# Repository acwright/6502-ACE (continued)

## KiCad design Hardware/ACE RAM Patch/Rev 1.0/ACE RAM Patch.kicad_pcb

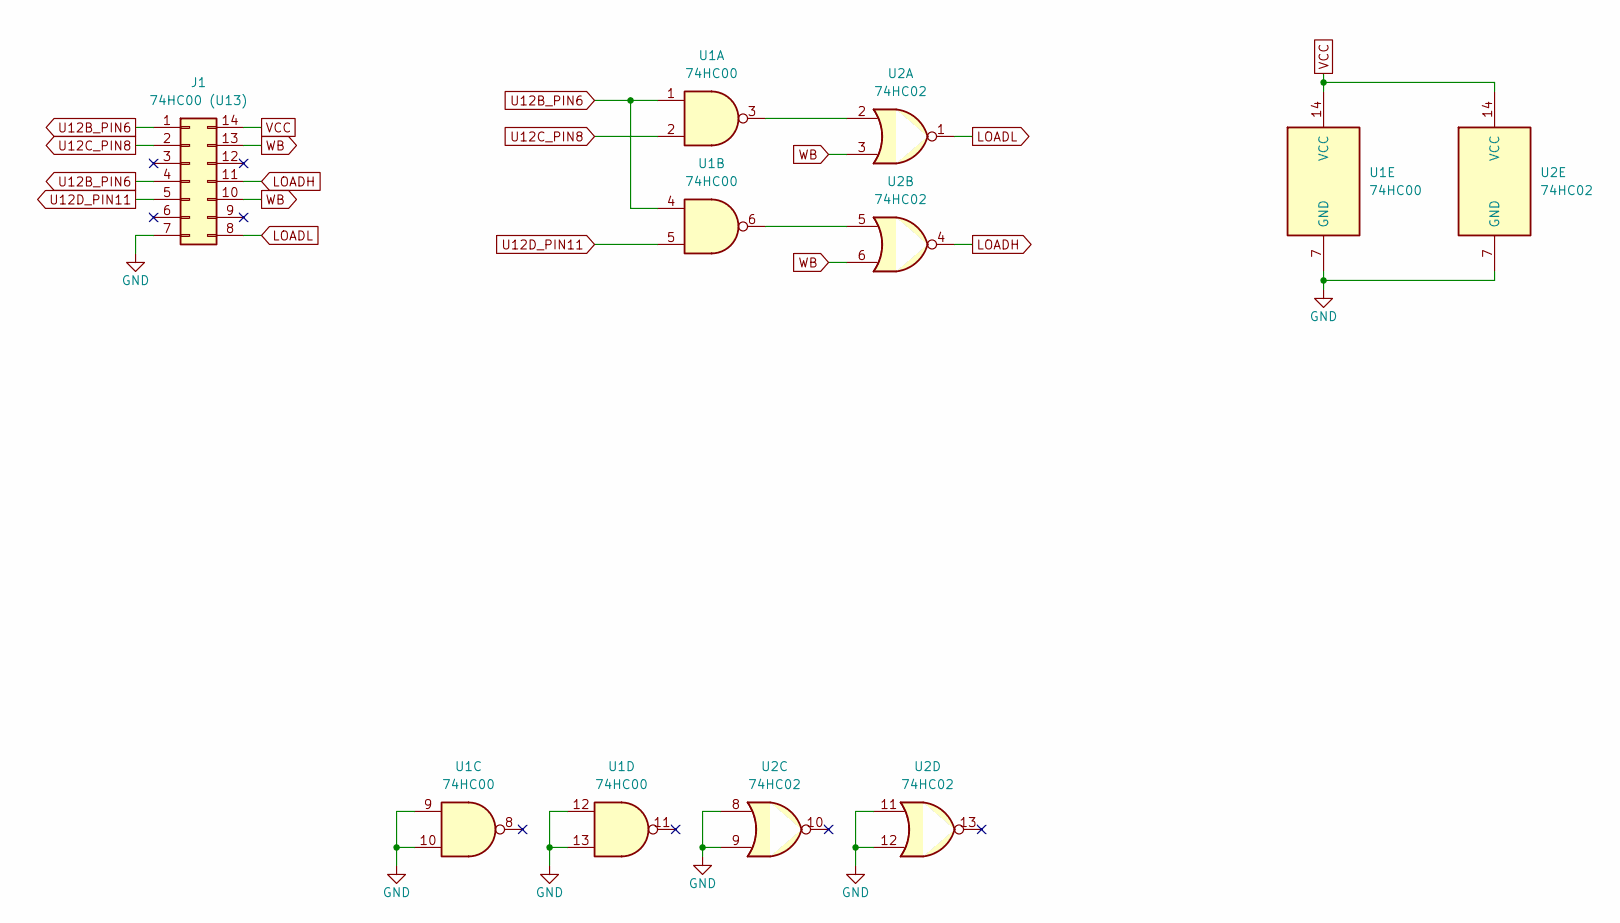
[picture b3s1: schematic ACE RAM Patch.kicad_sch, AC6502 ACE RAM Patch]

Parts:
J1: 74HC00 (U13); DIP-14_W7.62mm_LongPads; Digikey 296-1563-5-ND
U1: 74HC00; DIP-14_W7.62mm_LongPads; Digikey 296-1563-5-ND
U2: 74HC02; DIP-14_W7.62mm_LongPads; Digikey 296-1564-5-ND

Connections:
GND: J1.7, U1.7 (GND), U1.9, U1.10, U1.12, U1.13, U2.7 (GND), U2.8, U2.9, U2.11, U2.12
LOADH: J1.11, U2.4
LOADL: J1.8, U2.1
unnamed: U1.3, U2.2
unnamed: U1.6, U2.5
U12B_PIN6: J1.1, J1.4, U1.1, U1.4
U12C_PIN8: J1.2, U1.2
U12D_PIN11: J1.5, U1.5
VCC: J1.14, U1.14 (VCC), U2.14 (VCC)
WB: J1.10, J1.13, U2.3, U2.6

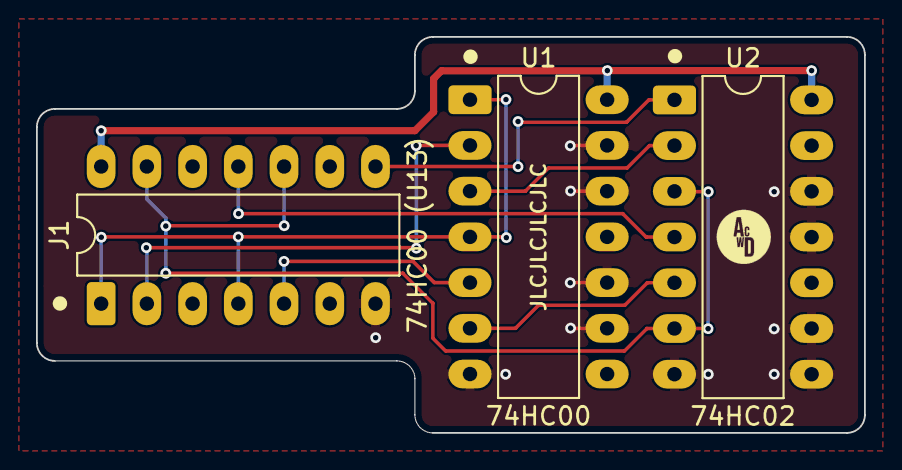
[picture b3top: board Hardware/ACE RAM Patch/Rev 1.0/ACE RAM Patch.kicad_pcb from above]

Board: 2 copper layers, 46.0 x 22.0 mm, 3 parts (0 on the bottom side), 10 nets.

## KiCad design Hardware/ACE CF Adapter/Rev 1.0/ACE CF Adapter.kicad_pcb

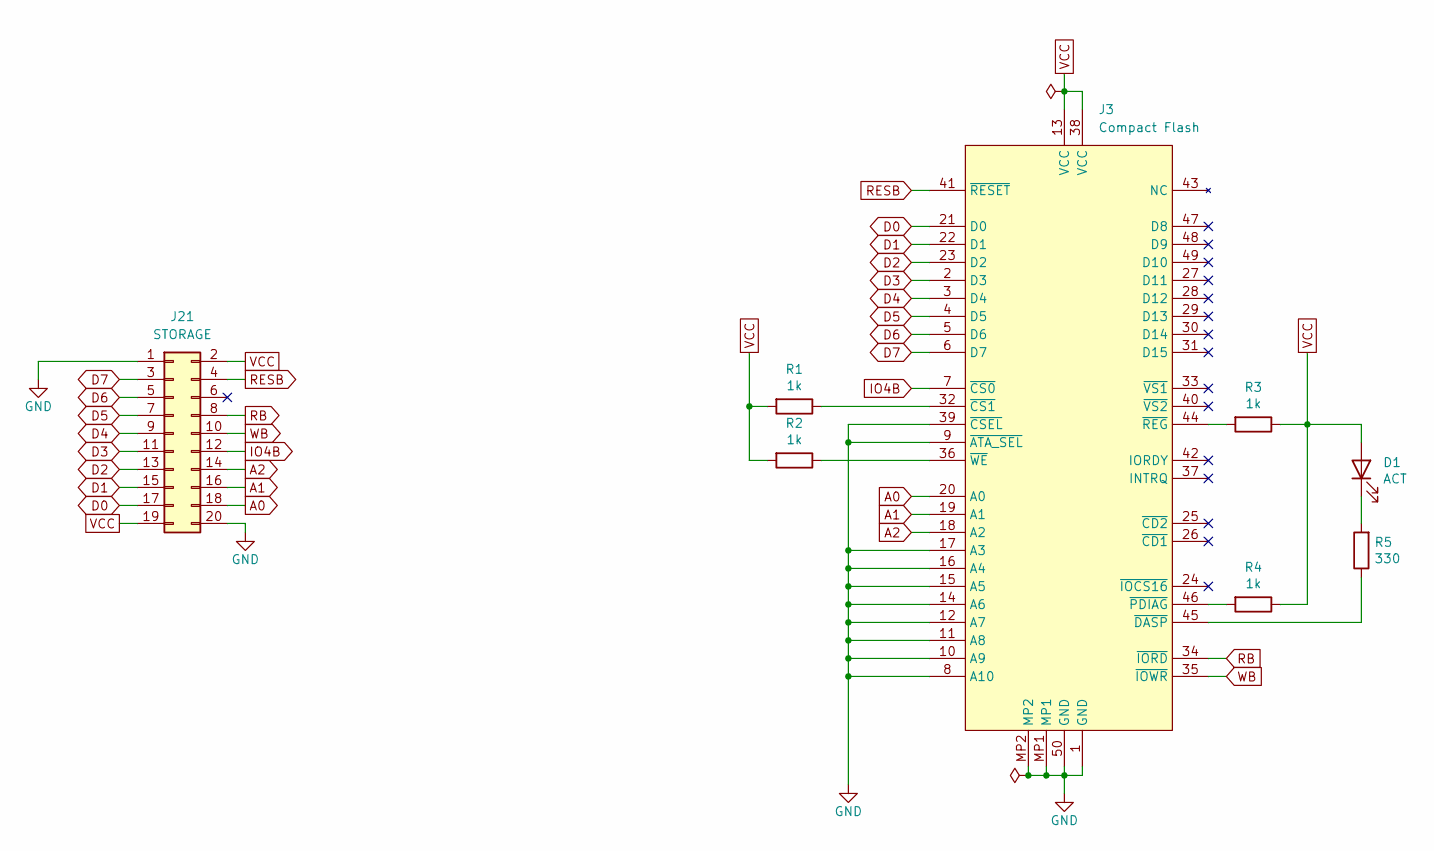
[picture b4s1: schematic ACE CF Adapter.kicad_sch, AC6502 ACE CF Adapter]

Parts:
D1: ACT; LED_D3.0mm; Digikey 732-5008-ND
J3: Compact Flash; CompactFlash Socket; Digikey 4827-101D-TAAB-R01-ND
J21: STORAGE; PinHeader_2x10_P2.54mm_Horizontal; Digikey 609-3338-ND
R1, R2, R3, R4: 1k; R_Axial_DIN0204_L3.6mm_D1.6mm_P5.08mm_Horizontal; Digikey 13-MFR-12FTF52-1KCT-ND
R5: 330; R_Axial_DIN0204_L3.6mm_D1.6mm_P5.08mm_Horizontal; Mouser 603-MFR-12FTF52-330R

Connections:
A0: J3.20 (A0), J21.18
A1: J3.19 (A1), J21.16
A2: J3.18 (A2), J21.14
D0: J3.21 (D0), J21.17
D1: J3.22 (D1), J21.15
D2: J3.23 (D2), J21.13
D3: J3.2 (D3), J21.11
D4: J3.3 (D4), J21.9
D5: J3.4 (D5), J21.7
D6: J3.5 (D6), J21.5
D7: J3.6 (D7), J21.3
GND: J3.1 (GND), J3.8 (A10), J3.9 (~ATA_SEL), J3.10 (A9), J3.11 (A8), J3.12 (A7), J3.14 (A6), J3.15 (A5), J3.16 (A4), J3.17 (A3), J3.39 (~CSEL), J3.50 (GND), J3.MP1, J3.MP2, J21.1, J21.20
IO4B: J3.7 (~CS0), J21.12
unnamed: D1.1 (K), R5.2
unnamed: J3.32 (~CS1), R1.1
unnamed: J3.45 (~DASP), R5.1
unnamed: J3.46 (~PDIAG), R4.2
unnamed: J3.44 (~REG), R3.2
unnamed: J3.36 (~WE), R2.1
RB: J3.34 (~IORD), J21.8
RESB: J3.41 (~RESET), J21.4
VCC: D1.2 (A), J3.13 (VCC), J3.38 (VCC), J21.2, J21.19, R1.2, R2.2, R3.1, R4.1
WB: J3.35 (~IOWR), J21.10

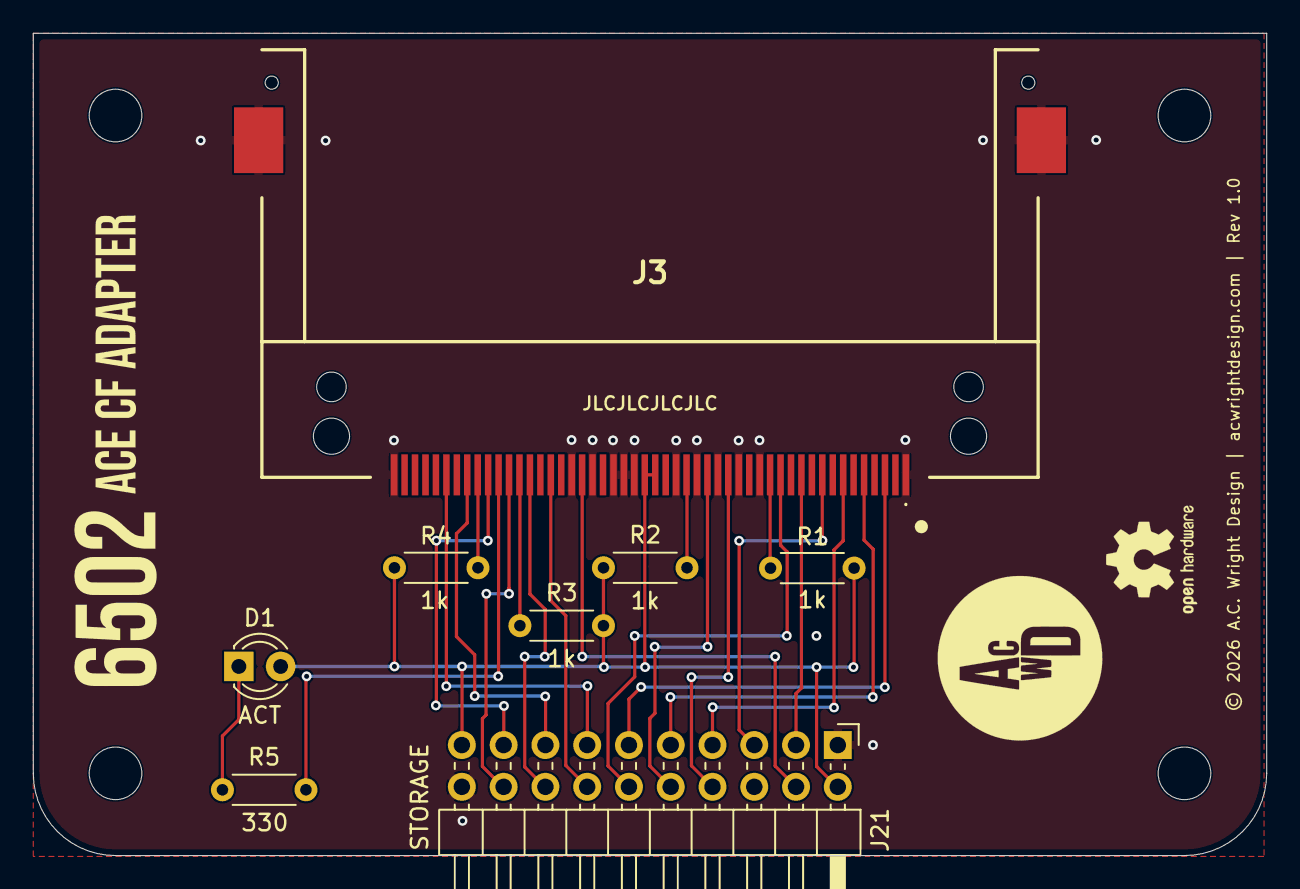
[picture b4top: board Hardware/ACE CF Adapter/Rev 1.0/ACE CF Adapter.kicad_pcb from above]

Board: 2 copper layers, 75.0 x 50.0 mm, 8 parts (0 on the bottom side), 23 nets.

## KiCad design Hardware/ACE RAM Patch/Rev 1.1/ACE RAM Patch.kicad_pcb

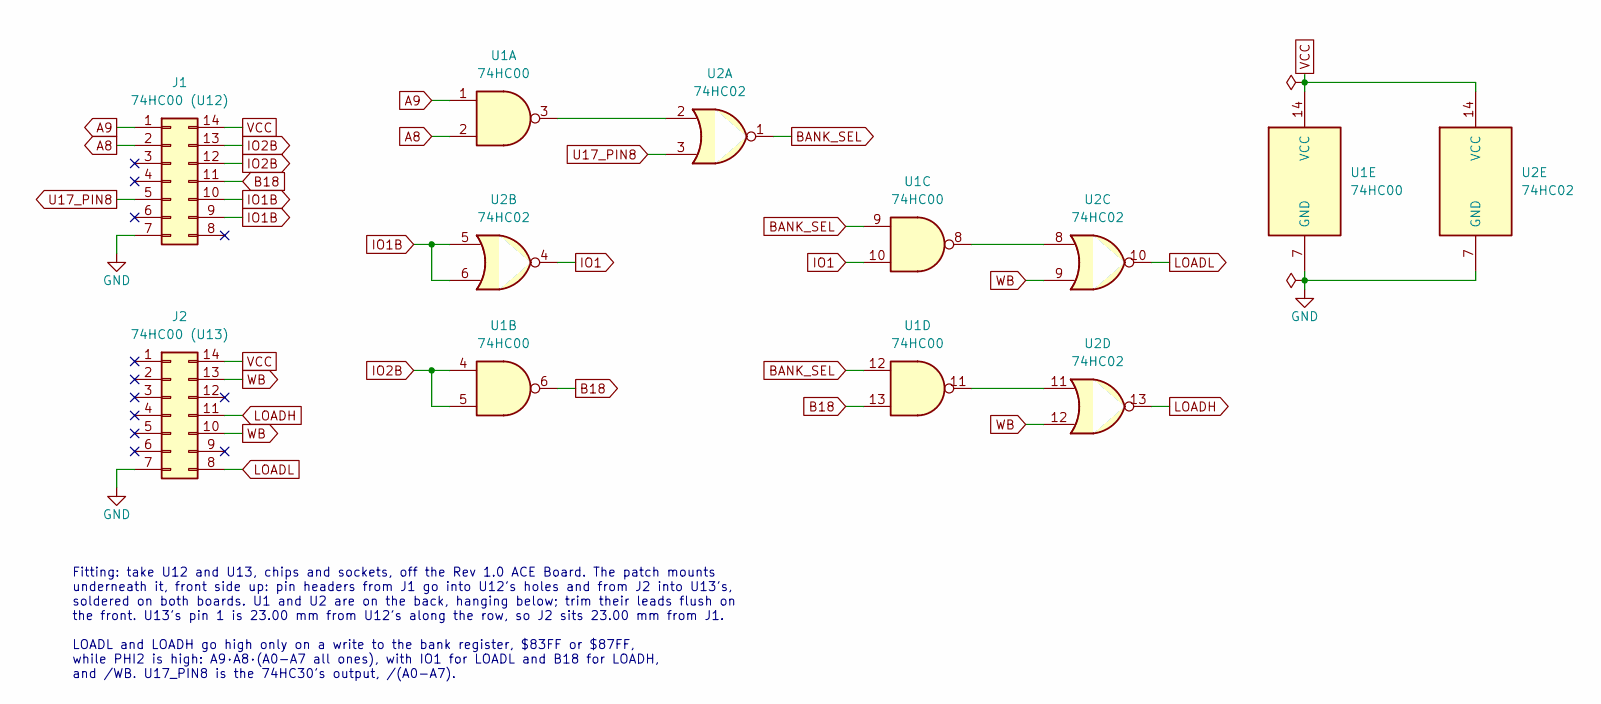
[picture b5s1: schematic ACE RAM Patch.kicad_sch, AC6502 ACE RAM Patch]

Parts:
J1: 74HC00 (U12); DIP-14_W7.62mm_LongPads; Digikey 296-1563-5-ND
J2: 74HC00 (U13); DIP-14_W7.62mm_LongPads; Digikey 296-1563-5-ND
U1: 74HC00; DIP-14_W7.62mm_LongPads; Digikey 296-1563-5-ND
U2: 74HC02; DIP-14_W7.62mm_LongPads; Digikey 296-1564-5-ND

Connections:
A8: J1.2, U1.2
A9: J1.1, U1.1
B18: J1.11, U1.6, U1.13
BANK_SEL: U1.9, U1.12, U2.1
GND: J1.7, J2.7, U1.7 (GND), U2.7 (GND)
IO1: U1.10, U2.4
IO1B: J1.9, J1.10, U2.5, U2.6
IO2B: J1.12, J1.13, U1.4, U1.5
LOADH: J2.11, U2.13
LOADL: J2.8, U2.10
unnamed: U1.3, U2.2
unnamed: U1.8, U2.8
unnamed: U1.11, U2.11
U17_PIN8: J1.5, U2.3
VCC: J1.14, J2.14, U1.14 (VCC), U2.14 (VCC)
WB: J2.10, J2.13, U2.9, U2.12

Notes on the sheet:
Fitting: take U12 and U13, chips and sockets, off the Rev 1.0 ACE Board. The patch mounts underneath it, front side up: pin headers from J1 go into U12's holes and from J2 into U13's, soldered on both boards. U1 and U2 are on the back, hanging below; trim their leads flush on the front. U13's pin 1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

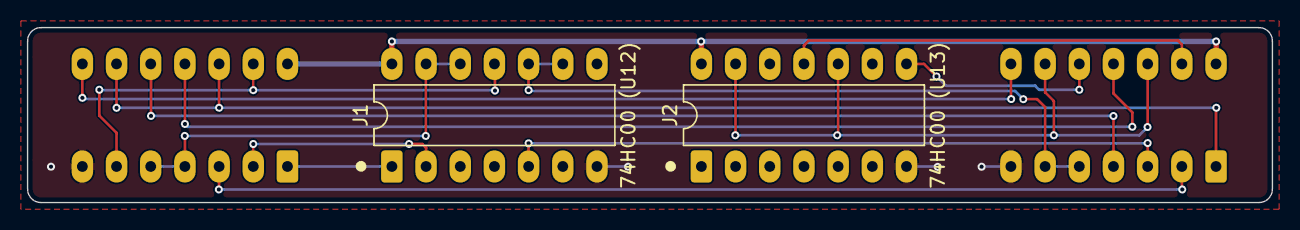
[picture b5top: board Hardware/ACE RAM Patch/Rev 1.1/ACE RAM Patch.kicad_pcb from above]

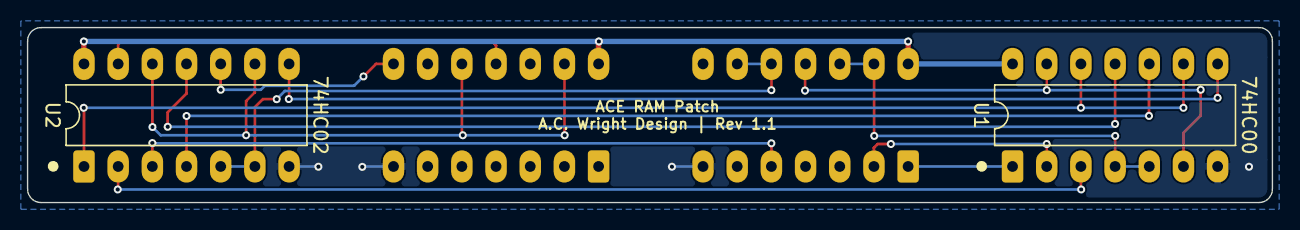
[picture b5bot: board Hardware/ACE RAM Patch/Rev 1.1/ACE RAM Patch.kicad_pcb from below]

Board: 2 copper layers, 92.5 x 13.0 mm, 4 parts (2 on the bottom side), 16 nets.

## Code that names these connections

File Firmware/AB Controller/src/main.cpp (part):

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// ============================================================================
// Keyboard Matrix Mapping 
// ============================================================================
// Rows: PA0-PA7 (VIA Port A)
// Columns: PB0-PB7 (VIA Port B)
//
//      PB0    PB1    PB2    PB3    PB4    PB5    PB6    PB7
// PA0:  `      1      2      3      4      5      6      7
// PA1:  8      9      0      -      =      BS     ESC    TAB
// PA2:  q      w      e      r      t      y      u      i
// PA3:  o      p      [      ]      \      INS    CAPS   a
// PA4:  s      d      f      g      h      j      k      l
// PA5:  ;      '      ENTER  DEL    SHIFT  z      x      c
// PA6:  v      b      n      m      ,      .      /      UP
// PA7:  CTRL   GUI    ALT    SPACE  FN     LEFT   DOWN   RIGHT
//
// Notes:
// - BS = Backspace (0x08), ESC = Escape (0x1B), TAB (0x09)
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
#define VIA_CA1 8
#define VIA_CA2 9
#define PS2CLK  10
#define PS2DATA 11
#define VIA_CB1 12
#define VIA_CB2 13

// 6502 system control (MightyCore "standard" pinout)
#define RESET_BTN 16   // PC0 - reset button (N.O., active low, internal pullup)
#define RESB      23   // PC7 - 6502 RESB, open-drain (active low; see assertRESB)
#define RTC_SQW   14   // PD6 - square-wave input from DS1511Y RTC
#define NMIB      15   // PD7 - 6502 NMIB output (active low)

// Power-on reset / reset button timing
#define POR_HOLD_MS       250  // Hold 6502 in reset at power-on for stable supply/clock
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// RTC SQW -> 6502 NMI jiffy clock (OPTIONAL, DISABLED BY DEFAULT)
// ----------------------------------------------------------------------------
// SQW-driven NMI behavior is off unless you explicitly opt in by uncommenting
// the line below and rebuilding the firmware. While disabled, NMIB (PD7) is
// left as a high-impedance input and the line is held high by the physical
// pullup resistor on the PCB, so the 6502 never sees an NMI from this board.
//
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// Joystick State
// ============================================================================
// The two sticks share the sixteen VIA port lines with the key matrix:
// JOYSTICK A on PA0-PA7 (the matrix rows) and JOYSTICK B on PB0-PB7 (the
// columns). Every signal is active low -- the switches close to ground -- so an
// untouched stick leaves its lines pulled high.
//
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// Jiffy clock (RTC SQW) state
volatile uint16_t jiffyCount = 0;
bool sqwIntEnabled = false;            // Has PCINT3 (SQW) been armed yet?
unsigned long resbReleasedAt = 0;     // millis() when RESB was last released
#endif

void onInterrupt();
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// ============================================================================
// VIA Port Access
// ============================================================================
// On the MightyCore "standard" pinout VIA_PA0-PA7 are D24-D31, which is exactly
// ATmega PORTA bits 0-7, and VIA_PB0-PB7 are D0-D7, which is exactly PORTB bits
// 0-7. Nothing else on this board lives on either register, so the whole port
// can be manipulated in a single instruction.
//
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//
// If the VIA_Px pin defines above ever change, these must change with them.

// CA2 (PD1) and CB2 (PD5) are the 6502 asking for a port back, active high.
#define CA2_RELEASE_REQUESTED() (PIND & _BV(PD1))
#define CB2_RELEASE_REQUESTED() (PIND & _BV(PD5))

// True when the 6502 has asked an encoder that is currently enabled -- and so
// currently driving a port -- to release it.
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// Maps each matrix position [row][col] to its base ASCII code (no modifiers)
// Special values: 0xFF = no key, 0xFE = modifier key (handled separately)
const uint8_t matrixMap[8][8] PROGMEM = {
  // PA0/Row 0: PB0    PB1    PB2    PB3    PB4    PB5    PB6    PB7
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  // PA1/Row 1
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  // PA2/Row 2
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  // PA3/Row 3
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  // PA4/Row 4
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  // PA5/Row 5
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  // PA6/Row 6
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  // PA7/Row 7
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};

// ============================================================================
// Jiffy Clock (RTC SQW -> 6502 NMI)
// ============================================================================
// The DS1511Y RTC drives a square wave into PD6 (RTC_SQW). Every JIFFY_DIVIDER
// rising edges we pulse NMIB (PD7) low to tick the 6502's jiffy clock. The NMI
// is generated directly in the ISR so its timing is independent of loop() load.
//
// NMIB is shared with the CART and BUS connectors, so PD7 drives it open-drain,
// like RESB: the PORTD latch for PD7 stays low (setup() leaves it there), and a
// pulse only switches the pin between output (low) and input (released, with
// the PCB's pull-up raising the line). PD7 never drives NMIB high, so a card can
// still raise its own NMI between pulses.
#ifdef ENABLE_SQW
ISR(PCINT3_vect) {
  static uint8_t lastSQW = 1;
  uint8_t cur = (PIND & _BV(PD6)) ? 1 : 0;

  if (cur && !lastSQW) {  // Rising edge of SQW
    if (++jiffyCount >= JIFFY_DIVIDER) {
      jiffyCount = 0;
      DDRD |= _BV(PD7);     // NMIB low (assert: output, latch already low)
      delayMicroseconds(5);
      DDRD &= ~_BV(PD7);    // NMIB released (input; the PCB pull-up raises it)
    }
  }
  lastSQW = cur;
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#endif

// RESB is shared: the DS1511Y's open-drain RST output and the CART and BUS
// connectors can pull it low too. So PC7 only ever pulls it low, and never
// drives it high, or the ATmega would hold the 6502 out of a reset something
// else asked for.
//
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// make the pin an output, so it goes straight to low without a high glitch.
void assertRESB() {
  digitalWrite(RESB, LOW);
  pinMode(RESB, OUTPUT);
}

// Release: an input with the internal pull-up on. The pull-up (20-50k) raises
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// pull-up the two share the job. Either way an open-drain device can still
// pull the line low.
void releaseRESB() {
  pinMode(RESB, INPUT_PULLUP);
}

// Poll the reset button and drive RESB on the 6502. The button is N.O. and
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  // pull-up holds the line high. With SQW disabled it stays that way, so the
  // 6502 never receives an NMI from this board. With SQW enabled, the jiffy ISR
  // pulses it low by switching the pin to an output and back.
  pinMode(NMIB, INPUT);

#ifdef ENABLE_SQW
  // RTC square-wave input (DS1511Y SQW). Pullup in case the output is open-drain.
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  pinMode(VIA_CA2, INPUT_PULLUP);
  pinMode(VIA_CB1, OUTPUT);
  pinMode(VIA_CB2, INPUT_PULLUP);
  pinMode(PS2CLK, INPUT_PULLUP);
  pinMode(PS2DATA, INPUT_PULLUP);

  digitalWrite(VIA_CA1, HIGH);
  digitalWrite(VIA_CB1, HIGH);
  
  attachInterrupt(digitalPinToInterrupt(PS2CLK), onInterrupt, FALLING);

#ifdef ENABLE_SQW
  // Configure the pin-change interrupt on PD6 (PCINT30) for the RTC SQW jiffy
  // clock, but do NOT arm it yet. Arming is deferred until SQW_BOOT_GRACE_MS
  // after RESB is released (see loop()) so a power-up 32.768 kHz SQW burst
  // cannot storm the 6502 with NMIs during the BIOS boot window.
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
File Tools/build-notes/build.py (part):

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<p>Use <code>-e atmega1284p</code> for a 1284P. The command also writes the fuses. The firmware's README has the details.</p>
{boxes("U6 programmed, and back in its socket.")}
<h3>Fit the pull-up</h3>
<p>The ATmega's internal pull-up raises RESB on its own, but a 10 kΩ is stiffer on a line that runs out to CART and BUS. Rev 1.1 has one. On Rev 1.0, U4's pins 2 and 4 are VCC and RESB, 5.08 mm apart, the same pitch as a resistor footprint.</p>
{boxes("10 kΩ across U4 pin 2 and U4 pin 4, on the underside. Pin 3 is between them: keep the legs off its joint.")}
</div>
<div style="padding-top:6pt">{fig(fig_resb(),"<b>Figure 6.</b> The RESB pull-up on the underside, keyboard edge toward you. U4's pin 1 is nearest the connectors.")}</div>
</div>
''')
pages.append(f'''
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<div class="side" style="grid-template-columns:2.2in 1fr">
<div>{fig(fig_u3(),"<b>Figure 7.</b> Find pin 16: the fifth pin up from the keyboard end of U3's left row.")}</div>
<div>{fig(fig_stack(),"<b>Figure 8. The stack, seen from inside the left row.</b> Not to scale. The riser's pin 16 stops short of the socket below, so the only path from the card's pin 16 to IRQB is through the diode.")}</div>
</div>
{boxes("Take a machined-pin DIP-40 socket: this is the riser. The pico9918's pins are solid and can't be bent or cut, so the change is made here.",
"Count to pin 16 on the riser, with its notch the same way as U3's. Cut off pin 16's tail below the plastic, so it can't reach U3's socket.",
"Solder the BAT85's band end (cathode) to what is left of the riser's pin 16.",
"Put the other leg (anode) into U3's socket at pin 16, and press the riser into U3's socket. Keep the diode under the card or on the board beside U3's left row, with its legs clear of the other pins.",
"Check with the meter's diode test, with the card out: red on IRQB (R4's left leg, Figure 2), black in the riser's pin 16. About 0.3 V this way, and open the other way.",
"Fit the card into the riser, with its pin 1 at the connector end. It now sits one socket higher: check that it clears any top panel.")}
''')

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("U2 pin 14","C27 VCC leg","U2 has power","Beep"),
("U2 pin 7","C27 GND leg","U2 has ground","Beep"),
("U2 pin 8","C27 GND leg","C27's leg not touching U2 pin 8","<b>No beep</b>"),
("U2 pin 10","U13 pin 8, ACE top","LOADL reaches the ACE","Beep"),
("U2 pin 13","U13 pin 11, ACE top","LOADH reaches the ACE","Beep"),
("U12 pin 1, ACE top","U12 pin 2, ACE top","A9 and A8 not bridged","<b>No beep</b>")]
mt="".join(f'<tr><td>{a}</td><td>{b}</td><td>{c}</td><td>{d}</td></tr>' for a,b,c,d in meter)
pages[-1]+=(f'''
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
